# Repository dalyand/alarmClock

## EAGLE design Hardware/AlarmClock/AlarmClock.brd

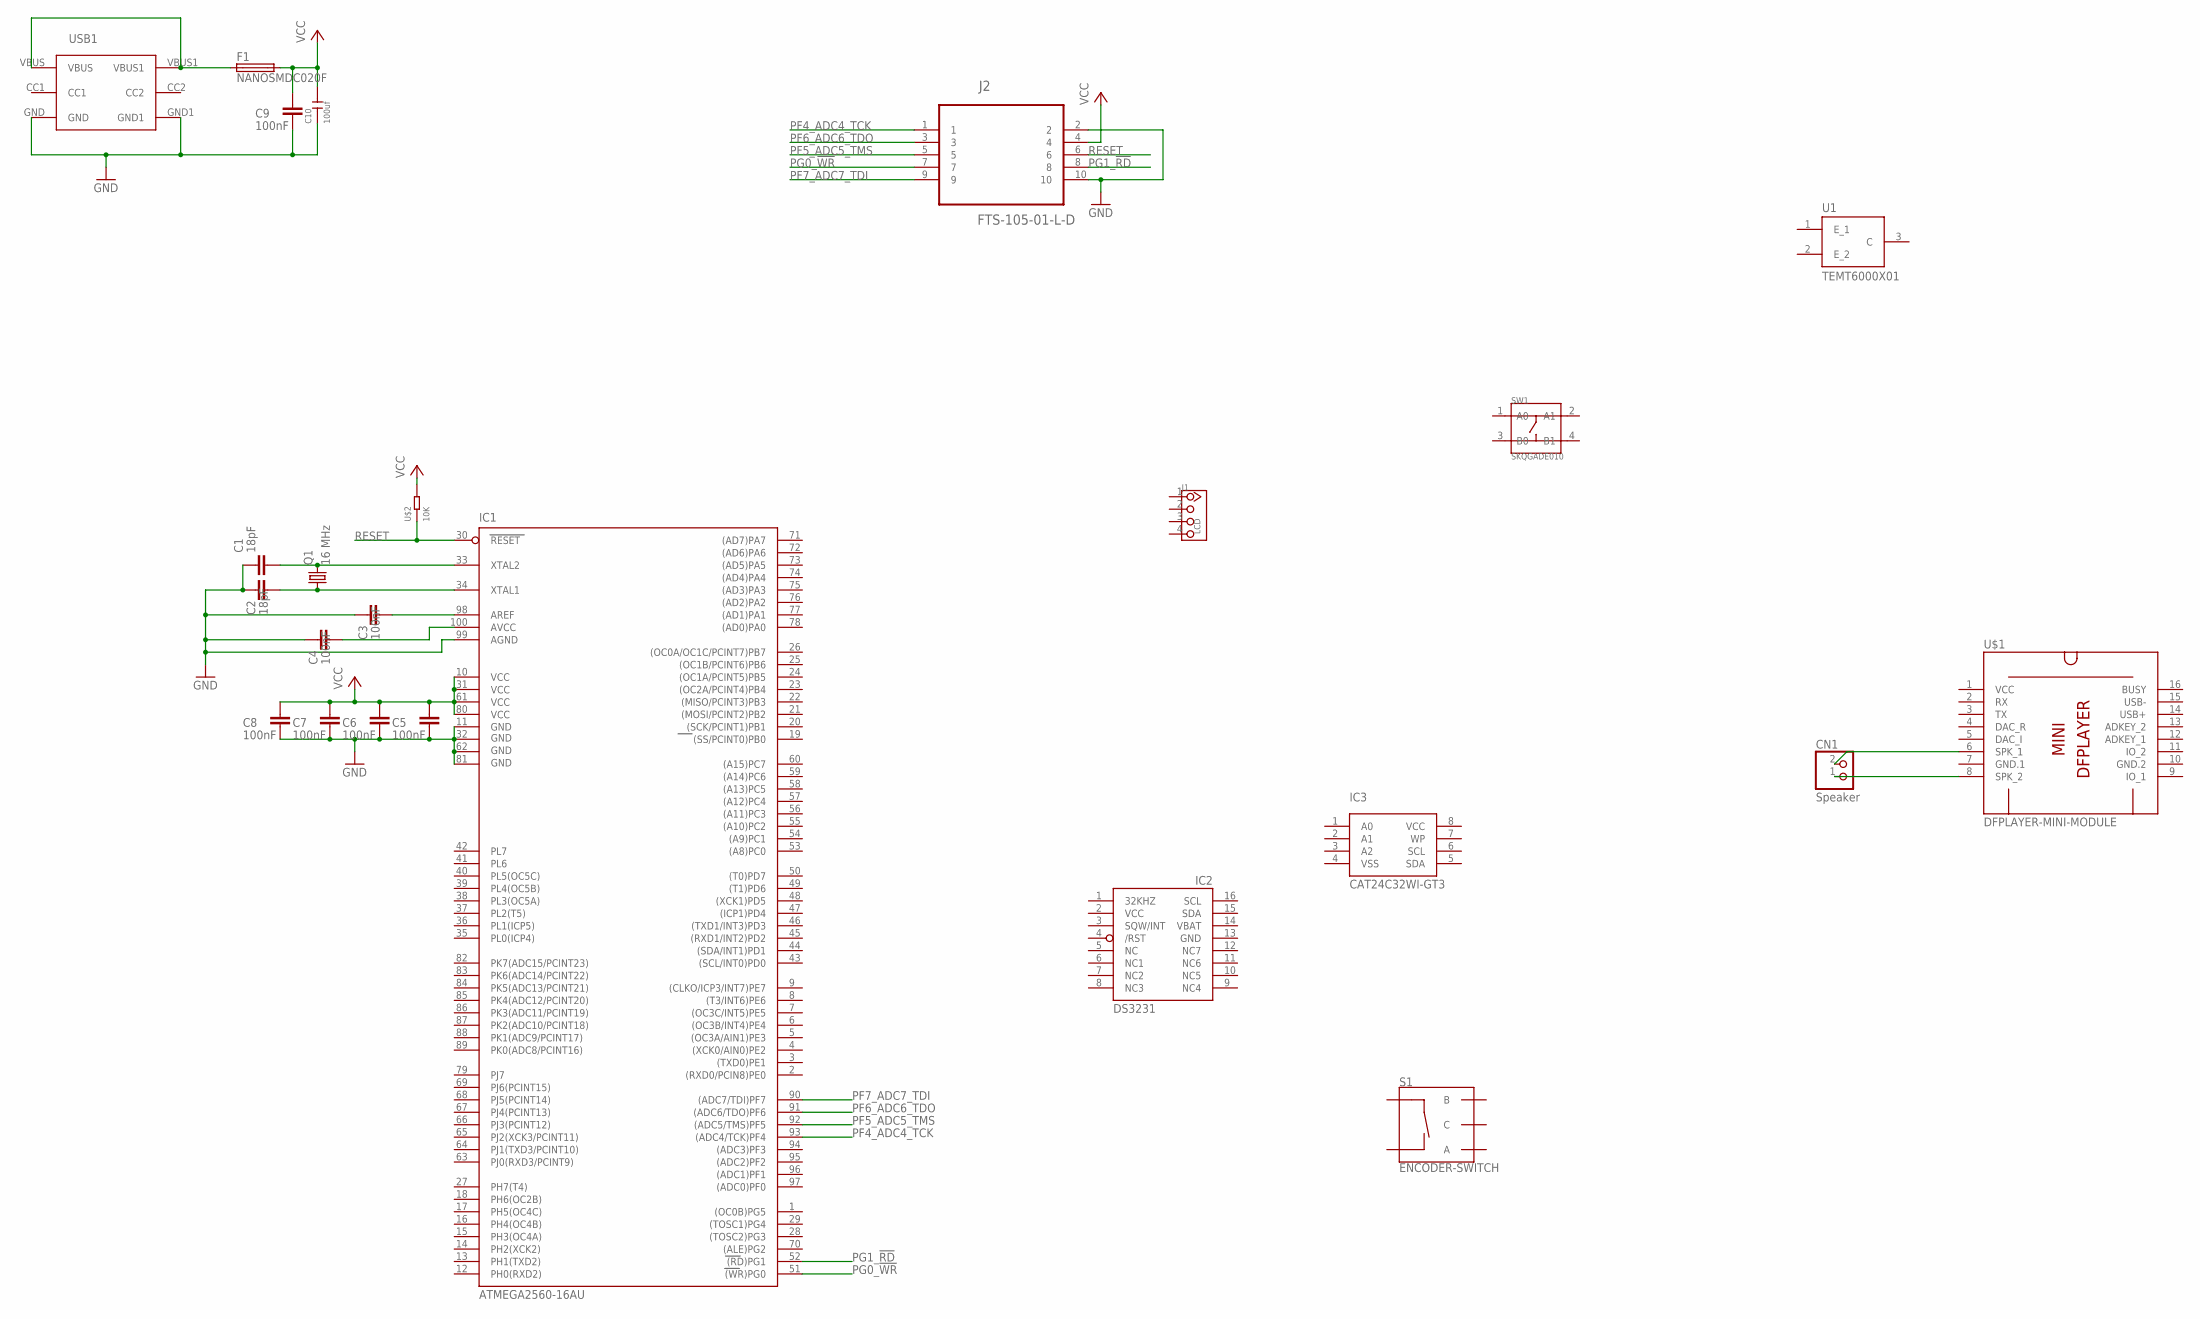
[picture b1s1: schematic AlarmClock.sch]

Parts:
C1, C2: 18pF; CAPC2012X110
C3, C4, C5, C6, C7, C8, C9: 100nF; CAPC2012X110
C10: 100uf; C1206
CN1: Speaker; JST-PH-2-THM
F1: NANOSMDC020F; FUSC3215X82N
IC1: ATMEGA2560-16AU; TQFP100
IC2: DS3231/SO; SO16W
IC3: CAT24C32WI-GT3; SOIC8
J1: LCD; 4P-2.0-W/O-BUCKLE
J2: FTS-105-01-L-D; SAMTEC_FTS-105-01-L-D
Q1: 16 MHz; HC49UP
S1: ENCODER-SWITCH; ROTARY_ENC_PLAIN
SW1: SKQGADE010; SW4-SMD-5.2X5.2X1.5MM
U1: TEMT6000X01; 1206
U$1: DFPLAYER-MINI-MODULE
U$2: 10K; R0805
USB1: USB_TYPE_C

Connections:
CC1: USB1.CC1
CC2: USB1.CC2
GND: C1.1, C2.1, C3.1, C4.1, C5.2, C6.2, C7.2, C8.2, C9.2, C10.1, IC1.11 (GND), IC1.32 (GND1), IC1.62 (GND2), IC1.81 (GND3), IC1.99 (AGND), IC2.13 (GND), J2.2, J2.10, USB1.GND, USB1.GND1
GND.1: U$1.7 (GND.1)
GND.2: U$1.10 (GND.2)
unnamed: CN1.2 (1), U$1.6 (SPK_1)
unnamed: CN1.1 (2), U$1.8 (SPK_2)
unnamed: C2.2, IC1.34 (XTAL1), Q1.1
unnamed: C1.2, IC1.33 (XTAL2), Q1.2
unnamed: C4.2, IC1.100 (AVCC)
unnamed: C3.2, IC1.98 (AREF)
unnamed: F1.1, USB1.VBUS, USB1.VBUS1
PF4_ADC4_TCK: IC1.93 ((ADC4/TCK)PF4), J2.1
PF5_ADC5_TMS: IC1.92 ((ADC5/TMS)PF5), J2.5
PF6_ADC6_TDO: IC1.91 ((ADC6/TDO)PF6), J2.3
PF7_ADC7_TDI: IC1.90 ((ADC7/TDI)PF7), J2.9
PG0_!WR: IC1.51 ((WR)PG0), J2.7
PG1_!RD: IC1.52 ((RD)PG1), J2.8
RESET: IC1.30 (RESET), J2.6, U$2.1
VBAT: IC2.14 (VBAT)
VCC: C5.1, C6.1, C7.1, C8.1, C9.1, C10.2, F1.2, IC1.10 (VCC), IC1.31 (VCC1), IC1.61 (VCC2), IC1.80 (VCC3), IC2.2 (VCC), IC3.8 (VCC), J2.4, U$1.1 (VCC), U$2.2
VSS: IC3.4 (VSS)

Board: 2 copper layers, 24 parts (0 on the bottom side), 16 nets, no tracks yet.

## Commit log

2020-09-18 Hardware started
2020-09-20 add pwr and jtag
2020-09-27 schema
2020-10-22 Working LCD example
2020-10-31 ucBoard rtc
2020-10-31 at24c32 memory hinzugefügt
2020-10-31 rtc uptade every sec
2020-11-05 i2c lcd funktioniert
2020-11-09 i2cLcd working

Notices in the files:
parts and their libraries:
diy-modules: Released under the Creative Commons Attribution 4.0 International License: http://creativecommons.org/licenses/by/4.0
SparkFun-Switches: Licensing: Creative Commons ShareAlike 4.0 International - https://creativecommons.org/licenses/by-sa/4.0
